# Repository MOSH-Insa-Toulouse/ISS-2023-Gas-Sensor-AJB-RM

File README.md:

# ISS 2023: Gas sensor 

### Authors
Romain Moulin & Aude Jean-Baptiste, 5ISS 2023-2024

# Introduction
The objective of this project is to integrate a gas sensor that we made ourselves during a training period at AIME (Atelier Interuniversitaire de Micro Electronique) and send its data over a Lora network to a dashboard to see and analyse the values.

# Initiation to Electronics and Arduino programming
As we both come from a computer science background (4IR-SC), we used the first labs as an introduction to Arduino and Kicad. We tested some small projects from simply making a LED from an Arduino blink to collecting data sent by a Nunchunck (A nintendo WII controller). We also designed an android application able to communicate and interact with an arduino.

 *Screenshot of our Android application*

These first sessions were really usefull to understand the basics of Arduino programming and electronics. These small projects were a good introduction to the real project of this course.

# Lora network integration

To begin our project, we first tried to connect an arduino to the Lora network. To do so, we used a RN2483 chip made by Microship which is a module that is able to communicate on a Lora network. As this chip only has tiny connectors, we needed to weld the component to a board that would have bigger connectors for the communication with the arduino. The following image features the board with an antenna for the 868MHz frequency band. 

 *RN2483 Module weld on the board*

After this step, we were able to connect our arduino to the INSA's Lora network. For this, we used *The Things Network* library for arduino, the code is available [here](./Arduino-Code/lora_connection/lora_connetion.ino).
For this, we had used the otaa authentication method. We got the device ID using the library and the application ID and key on the [chirpstack's INSA website](https://srv-chirpstack.insa-toulouse.fr/#/login) (please note that this server is only available if you are directly connected to INSA's network, or using a VPN). 

 *Authentication of the arduino to the Lora network*

# Integration of the MQ-3B gas sensor

With the established connection, we had to send data to the gateway in order to retrive it and display it on a dashboard. As a first implementation of this application we connected an alreay made gas sensor which is the MQ-3B gas sensor to our arduino. The final montage of our circuit is the following:

 *Montage of the circuit with the MQ-3B gas sensor*

After that we changed our arduino code to read the value from the gas sensor and send it to our LoRa network. As the max value we can get from the sensor is 1024, we encoded the information on 2 bytes before sending it.

 *Our arduino setup and loop functions*

# Design of a node-red application

As the data is received by the LoRa network, we could visualize it on the chirpstack web page. However, it is not fitted for a real usage of our gas sensor. A user of gas sensor would like to see the state of the sensor in real time in a dashboard. To do so, we decided to use node-red and MQTT.

MQTT is a communication protocol particulary used for IoT devices. With this protocol there are two kind of nodes, the publisher and the subscribers. Publishers publish data in a topic and subscriber get all the data published on a specific topic. This protocol is supported by chirpstack which automatically upload the data it receives in a MQTT topic. 

Node-red is a web-browser flow editor that helps to easily connect flows. It provides visual coding with blocks for the ease of conception. It also implements dashboard library to display the data is user friendly dahsboards. We used a MQTT subscribe block to get the data from chirpstack that we pipe into a javascript function that decodes the data (it is encoded in base64 by chirpstack). Finaly we send the decoded data to a dashboard block to visualize the data.

 *The node-red flow*

# Test of the MQ-3B solution

To test our sensor, we putted hydroalcoholic gel near it to see if we could see it on our dashboard. This experience was a succes and we were able to see on the dashboard the increase of the gas rate near the sensor.

 *Dashboard for the witness experience in ambient air*

 *Dashboard for the experience with alcoholic gel*

# Integration of our gas sensor from AIME 

The specifications of our gas sensor are detailed in the datasheet (see below). In order to replace the commercial sensor (MQ-3B) by our gas sensor in our previously detailed monitoring solution with Lora and node-red, we need to follow various steps. 

Indeed, our sensor per se is passive; changes in its resistance allow us to monitor gas presence. We will power and control the sensor through an arduino uno and get its data with the ADC (analog digital converter),  like we did with the MQ-3B. 

The screenshots on the following part have been extracted from our Kicad project, that you can find [here](./MOSH). 

## Transimpedance amplifier

The first stage to treat sensor data is a transimpedance amplifier that will allow us to shape the signal for it to be detected by the arduino's ADC. This stage contains 3 low-pass filters with the following cut-off frequencies and roles: 
- filter 1: 16Hz - this filter is here to eliminate as much noise from the sensor as possible
- filter 2: 1.6Hz - this filter should get rid off the 50Hz noise
- filter 3: 1.6kHz - this filter should adapt the signal to the arduino's ADC 

This circuit was simulated on LTSpice to test the properties of the different filters and of the transimpedance amplifier per se. You can find all the related work in [this directory](./ltspice-stuff)

The transimpedance amplifier is featured in the following image. 

 *Our transimpedance amplifier stage*

You might notice that what we called R3 on this schematic is not a resistor. Indeed, we need to apply a variable resistance to the reverser entry of the operationnal amplifier. This variable resistor is detailed in the next subsection. 

## Digital potentiometer

We use a digital potentiometer as a variable resistor. We choose a MCP41100. This component is powered on 5V and controlled by the arduino via SPI (3 pins: Clock, MOSI and CS). 

The following image features the schematic for this component. 

 *Montage for the digital potentiometer*

## Heating resistor controlled via PWM 

Our sensor is a "smart sensor". It contains a heating resistor (a polysilicon resistor) as well as a temperature sensor (an aluminium resistor). The heating resistor needs to be controlled by the arduino via PWM, which is possible thanks to the following montage with a IRF540N transistor. 

 *PWM montage with transistor*

## Sensor connections 

We designed a symbol in Kicad for our sensor. You can find the library [here](./Library_AJB_RM_0). The symbol is associated with the Package_TO_SOT_THT:TO-5-10 footprint, on which our sensor has been mounted. 

The schematic of the sensor connections is featured below. 

 *Our gas sensor connections on the schematic*

## PCB design 

We designed a PCB to integrate our sensor with all the previously described stages. 

This PCB is featured in the following figure. 

 *Our PCB for sensor integration*

 *A nice 3D view of our PCB*

We followed these clearance and track size rules: 

Name|Clearance|Track Width|Via size|Via Hole
---|---|---|---|---
Default	| 0.2 mm	| 0.25 mm	| 0.6 mm	| 0.4 mm	
power	| 0.2 mm	| 1.2 mm	| 0.6 mm	| 0.4 mm	

**Minimum clearance: 0.8mm**

**Minimum track width: 0.8mm**

**Minimum via diameter: 1.5mm**

This PCB is far from perfect as we are two computer science students. We did not had the time to print it and integrate it with a real sensor. 

We can cite some ways to improve it if we were to continue the project:
- the vias could be bigger and better placed, especially the one for the ADC track.
- there is some clearance violations on the gas sensor, because we had to adopt less stricts rules to be able to route the sensor's tracks.
- there are quite a lot of right angles on the 5V track that we were not able to eliminate but that could be problematic.
- some angles on the PCB are acute, even if we tried to avoid them.
- you can notice that we connected one of the non connected pins of the sensor to ISENS2 to facilitate routing.

# Datasheet of our gas sensor from AIME 

We realized a datasheet for our gas sensor that you can find [here](./Datasheet.pdf). 

You might realize that it does not include the graphs that show the evolution of sensor's resistance with gas presence, because we were not given this year's data from AIME training period (and our nano particles synthesis did not worked as expected anyway). Furthermore, the previous years' data were uncomplete as they were not labeled with the gas' names.  

# To go further

As we did not had time to print the PCB, some obvious steps to bring our work further would be: 
- print the PCB
- weld all the components
- test the electrical circuits
- write code to control the heating resistor and the potentiometer
- create a retrocontrolled loop to manage sensor's temperature
- test the sensor reactivity to NH<sub>3</sub> and C<sub>2</sub>H<sub>6</sub>O 
- test the whole system with Lora transmission of the data and display in the node-red application
- enjoy a fully smart sensor ;-) 

# Conclusion

This project was a great start to finish introduction to the world of sensors, from fabrication to integration of the data on user-friendly dashboards. We were able to develop or reinforce skills in various fields like Lora communication, node-red applications, or PCB design.

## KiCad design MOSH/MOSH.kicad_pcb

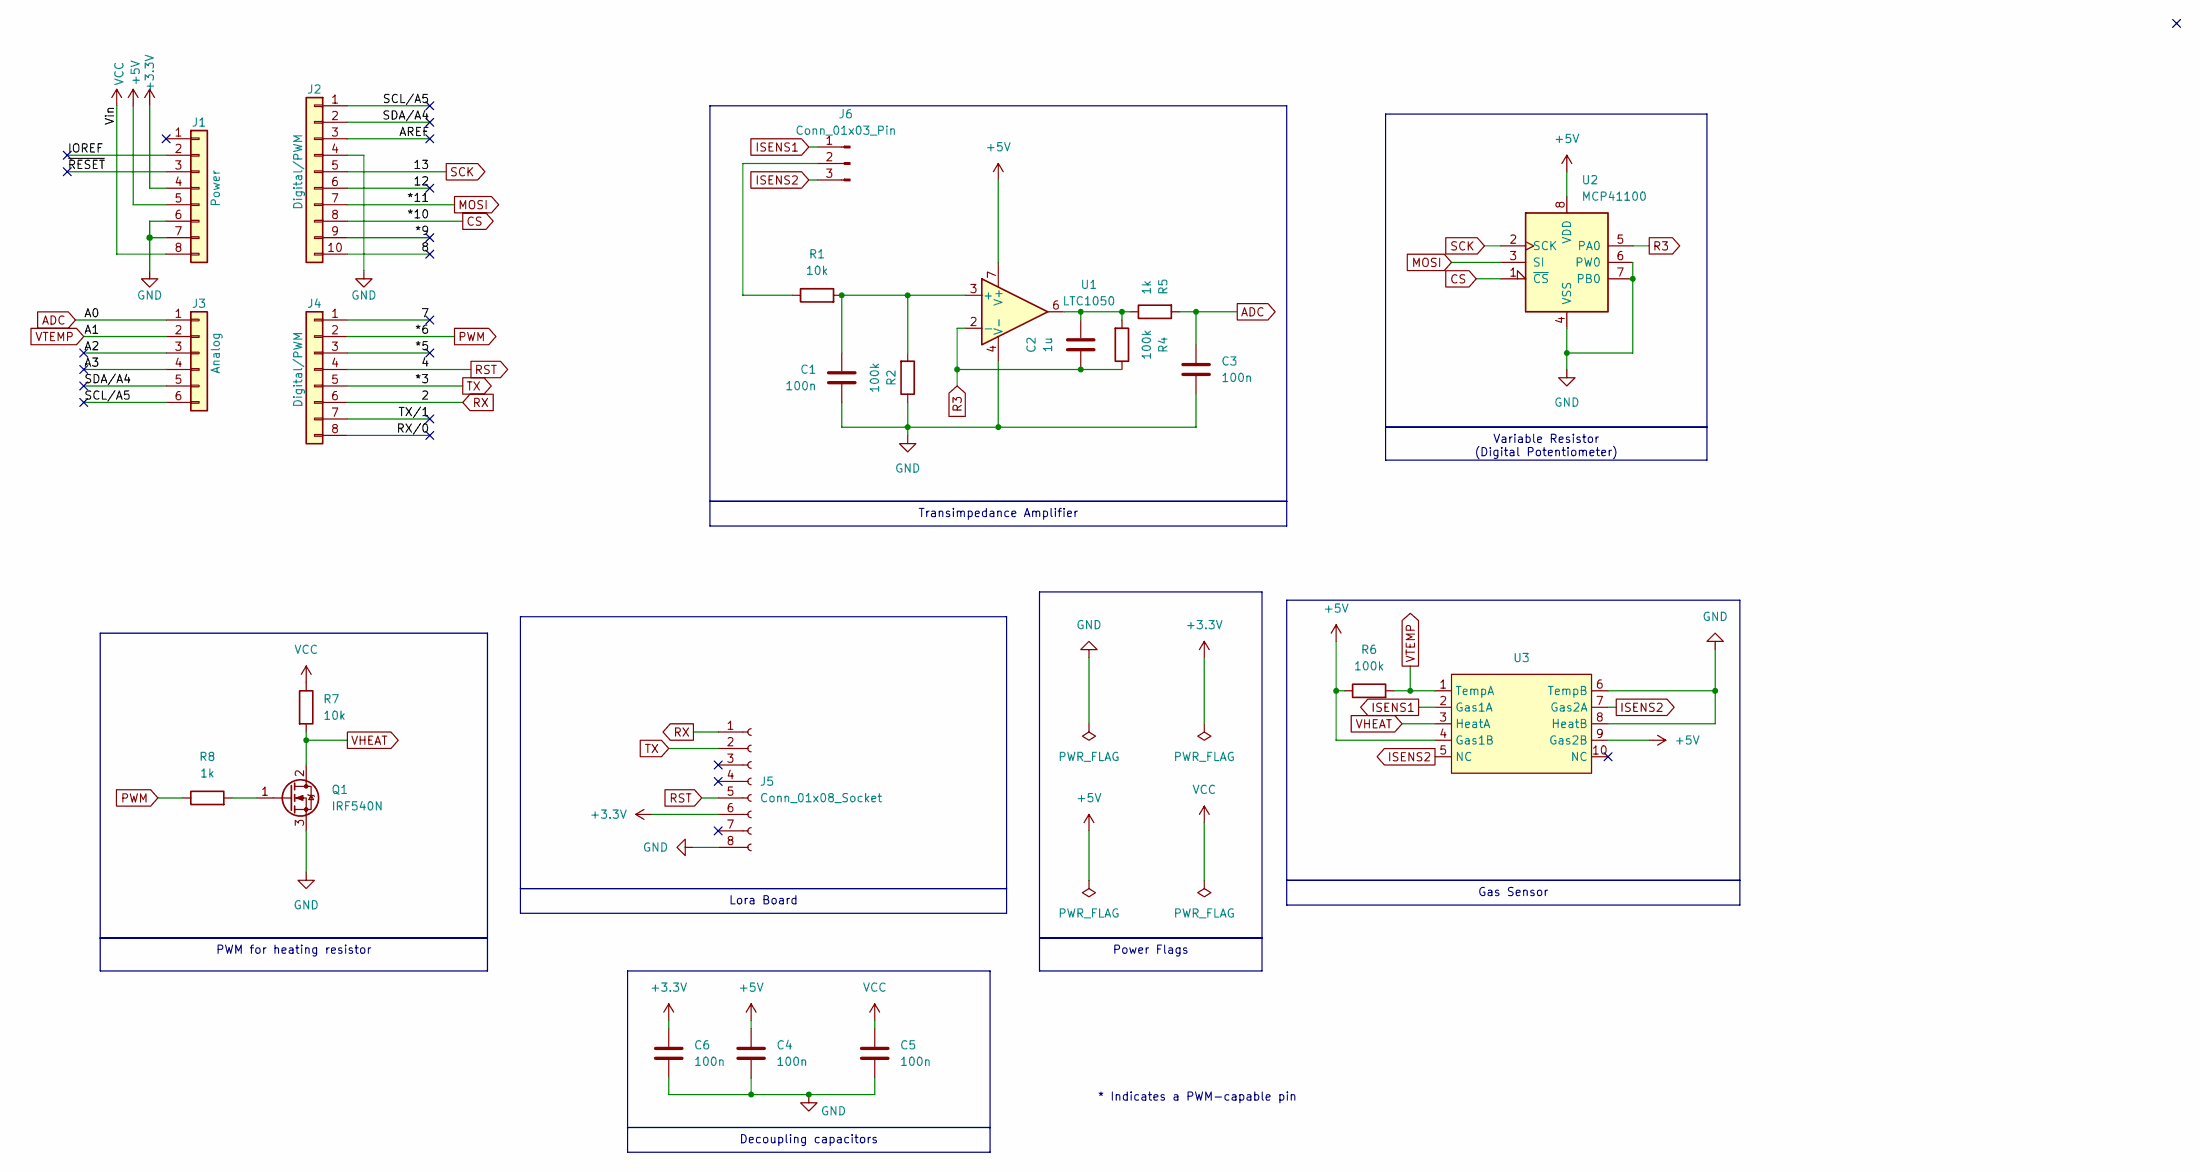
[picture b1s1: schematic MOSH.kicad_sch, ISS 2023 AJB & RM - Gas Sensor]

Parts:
C1, C3, C4, C5, C6: 100n; C_Disc_D4.7mm_W2.5mm_P5.00mm
C2: 1u; C_Rect_L7.0mm_W4.5mm_P5.00mm
J1: Power; PinSocket_1x08_P2.54mm_Vertical
J2: Digital/PWM; PinSocket_1x10_P2.54mm_Vertical
J3: Analog; PinSocket_1x06_P2.54mm_Vertical
J4: Digital/PWM; PinSocket_1x08_P2.54mm_Vertical
J5: Conn_01x08_Socket; PinSocket_1x08_P2.54mm_Vertical
J6: Conn_01x03_Pin; PinHeader_1x03_P2.54mm_Vertical
Q1: IRF540N; TO-220-3_Vertical
R1, R7: 10k; R_Axial_DIN0207_L6.3mm_D2.5mm_P10.16mm_Horizontal
R2, R4, R6: 100k; R_Axial_DIN0207_L6.3mm_D2.5mm_P10.16mm_Horizontal
R5, R8: 1k; R_Axial_DIN0207_L6.3mm_D2.5mm_P10.16mm_Horizontal
U1: LTC1050; DIP-8_W7.62mm
U2: MCP41100; DIP-8_W7.62mm
U3: TO-5-10

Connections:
+3.3V: C6.1, J1.4, J5.6
+5V: C4.1, J1.5, R6.1, U1.7 (V+), U2.8 (VDD), U3.4 (Gas1B), U3.9 (Gas2B)
/7: J4.1
/8: J2.10
/12: J2.6
/*5: J4.3
/*9: J2.9
/A2: J3.3
/A3: J3.4
/AREF: J2.3
/IOREF: J1.2
/RX/0: J4.8
/SCL/A5: J2.1, J3.6
/SDA/A4: J2.2, J3.5
/TX/1: J4.7
/~RESET: J1.3
ADC: C3.1, J3.1, R5.2
CS: J2.8, U2.1 (~CS)
GND: C1.1, C3.2, C4.2, C5.2, C6.2, J1.6, J1.7, J2.4, J5.8, Q1.3 (S), R2.1, U1.4 (V-), U2.4 (VSS), U2.6 (PW0), U2.7 (PB0), U3.6 (TempB), U3.8 (HeatB)
ISENS1: J6.1, U3.2 (Gas1A)
ISENS2: J6.3, U3.5 (NC), U3.7 (Gas2A)
MOSI: J2.7, U2.3 (SI)
unnamed: C2.2, R4.2, R5.1, U1.6
unnamed: J6.2, R1.1
unnamed: Q1.1 (G), R8.2
unnamed: C1.2, R1.2, R2.2, U1.3 (+)
PWM: J4.2, R8.1
R3: C2.1, R4.1, U1.2 (-), U2.5 (PA0)
RST: J4.4, J5.5
RX: J4.6, J5.1
SCK: J2.5, U2.2 (SCK)
TX: J4.5, J5.2
VCC: C5.1, J1.8, R7.1
VHEAT: Q1.2 (D), R7.2, U3.3 (HeatA)
VTEMP: J3.2, R6.2, U3.1 (TempA)

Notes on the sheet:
Decoupling capacitors
Variable Resistor (Digital Potentiometer)
PWM for heating resistor
Transimpedance Amplifier
Lora Board
Gas Sensor
Power Flags
* Indicates a PWM-capable pin

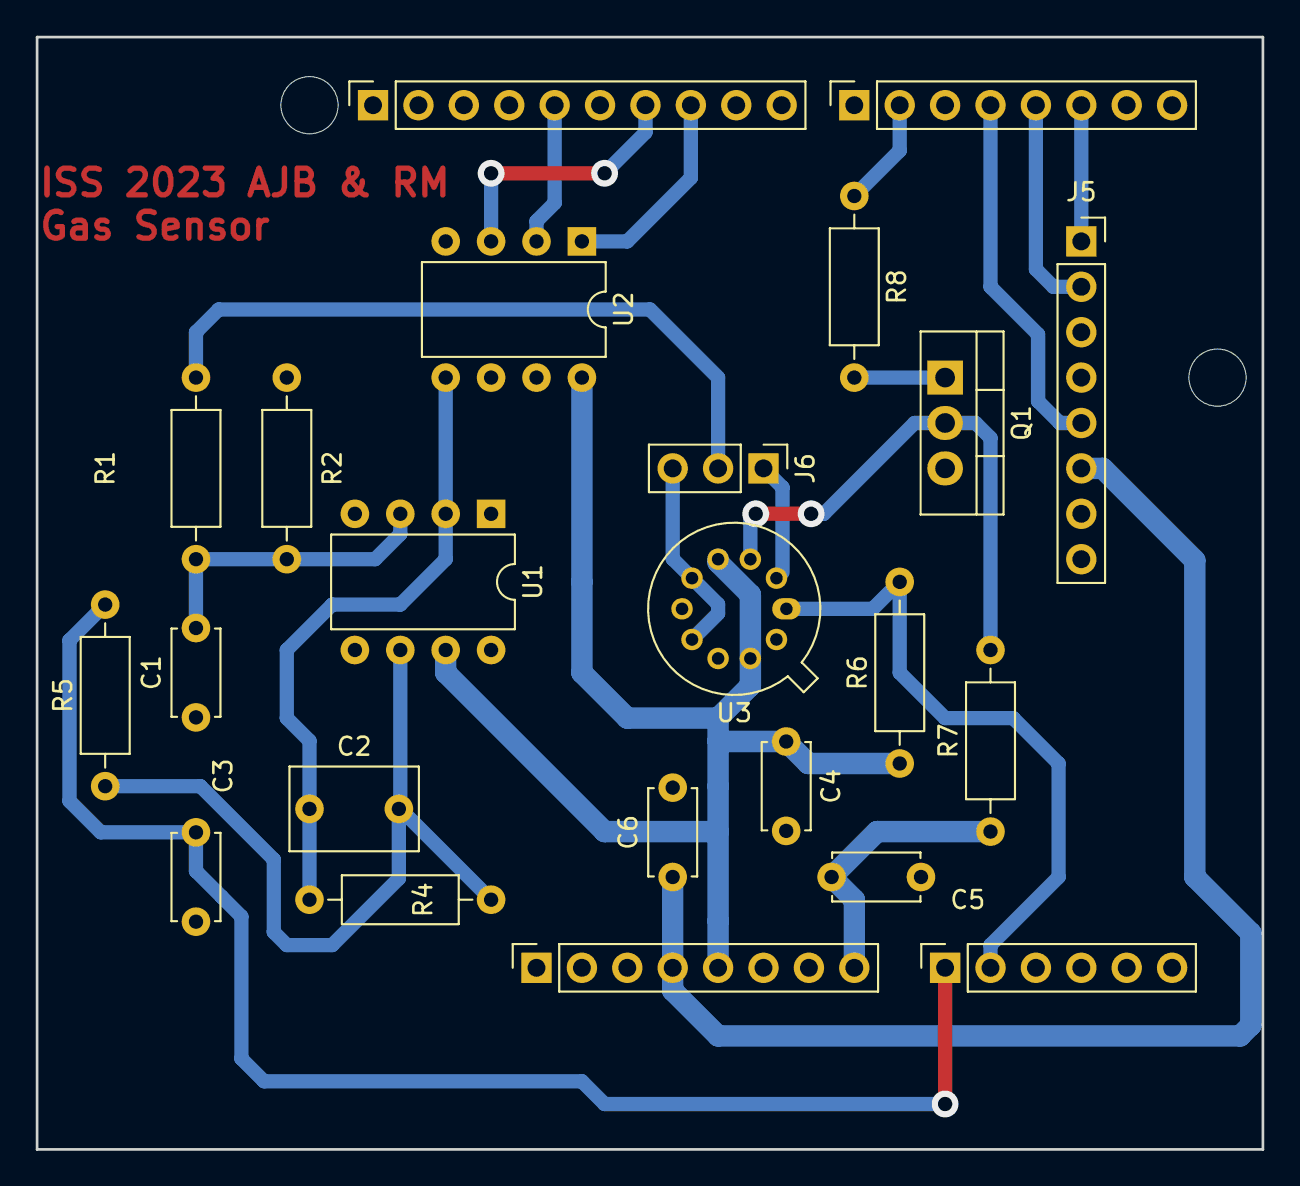
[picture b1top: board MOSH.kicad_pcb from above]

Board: 2 copper layers, 68.6 x 62.2 mm, 25 parts (0 on the bottom side), 23 nets.

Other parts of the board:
MH1, MH3: MountingHole_3.2mm

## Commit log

2023-12-08 ltspice files
2023-12-08 ranger
2023-12-13 Kicad project
2023-12-13 pcb schematic transimpedance amplifier, variable resistance, lora board and gas sensor
2023-12-13 Ajout dossier image
2023-12-13 Rename Capture d'écran 2023-12-13 111622.png to Application_Bluetooth
2023-12-13 Rename Capture d'écran 2023-12-13 111703.png to Gas_Sensor_Dashboard
2023-12-13 Rename Application_Bluetooth to Application_Bluetooth.png
2023-12-13 Rename Gas_Sensor_Dashboard to Gas_Sensor_Dashboard.png
2023-12-13 Ajout image dashboard avec ethanol
2023-12-13 pcb schematic fini
2023-12-13 j'essaie de mettre la librairie sur git aussi
2023-12-13 correct some typos
2023-12-15 rajout code et image
2023-12-15 add all footprints and start rooting
2023-12-15 router avec Allan!
2023-12-15 ajouter des règles de routage pour mettre dans readme /rapport
2023-12-19 je pensais avoir commit la dernière fois
2023-12-19 je route
2023-12-20 routage fini oui j'ai fait des vias, du coup il manque plus que le plan de masse
2023-12-20 commencer le plan de masse, mon routage il est tout cassé du coup
2023-12-21 Ajout Image
2023-12-21 presque fini routage il manque plus que quelques détails ; penser à checker les règles electrique
2023-12-22 j'ai fini de router, c'est pas opti mais ça existe
2023-12-30 run design rules check and correct some things
2023-12-30 correct some spelling mistakes & co
2023-12-30 add alt to images
2023-12-30 décaler les titres
2023-12-30 add schematic screenshots
2023-12-30 add title
2023-12-30 Il est raisonnable de commit
2023-12-30 change images siwe
2023-12-30 images for readme
2023-12-30 finir partie sur pcb
2023-12-30 change title
2023-12-30 to go further and conclusion
2023-12-30 correct spelling mistake
2023-12-30 Ajout de la datasheet
